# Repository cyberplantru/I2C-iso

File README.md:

##CyberPlant I2C *iso* Mini

The I2C *iso* Mini v3.0 are hot swappable digital isolators with nonlatching, bidirectional communication channels that
are compatible with I2C interfaces. This eliminates the need for
splitting I2C signals into separate transmit and receive signals
for use with standalone optocouplers. The I2C *iso* Mini provides two bidirectional channels, supporting a complete isolated I2C interface.

##Features:
- Regulated 3.3 V or 5 V output
- Up to 500 mW output power
- Bidirectional I2C communication
- input-output pull up 4k7
- Can use as Shield for Arduino Pro Mini
- PCB Size : 33.02 mm×17.78 mm

## Applications
- Isolated sensor interfaces
- Isolated I2C, SMBus, or PMBus interfaces
- Multilevel I2C interfaces
- Power supplies
- Networking
- RS-232/RS-422/RS-485 transceivers

#### Regulated 3.3 V or 5 V output

By default supply voltage set to output 5V. For use other mode need to cut copper wire on layer top and use jumper as switch

## Isolation of sensors

Use to eliminate electrical noise. The I2Ciso recommended to when reading pH and Conductivity together. Compatible with [pH Mini](https://github.com/cyberplantru/pH-Mini-v30-sample-code) and [EC Mini](EC-Mini-v30-Sample-Code). 

----------

### Package include:

-     1 x I2C iso Mini v3.0
-     2 x 12 PLS connectors
-     2 x 4 angle PLS
-     1 x jumper

----------

### Documentation:

- [Hardware](https://github.com/cyberplantru/I2C-iso/)
- [link to CyberPlant](http://www.cyber-plant.com).

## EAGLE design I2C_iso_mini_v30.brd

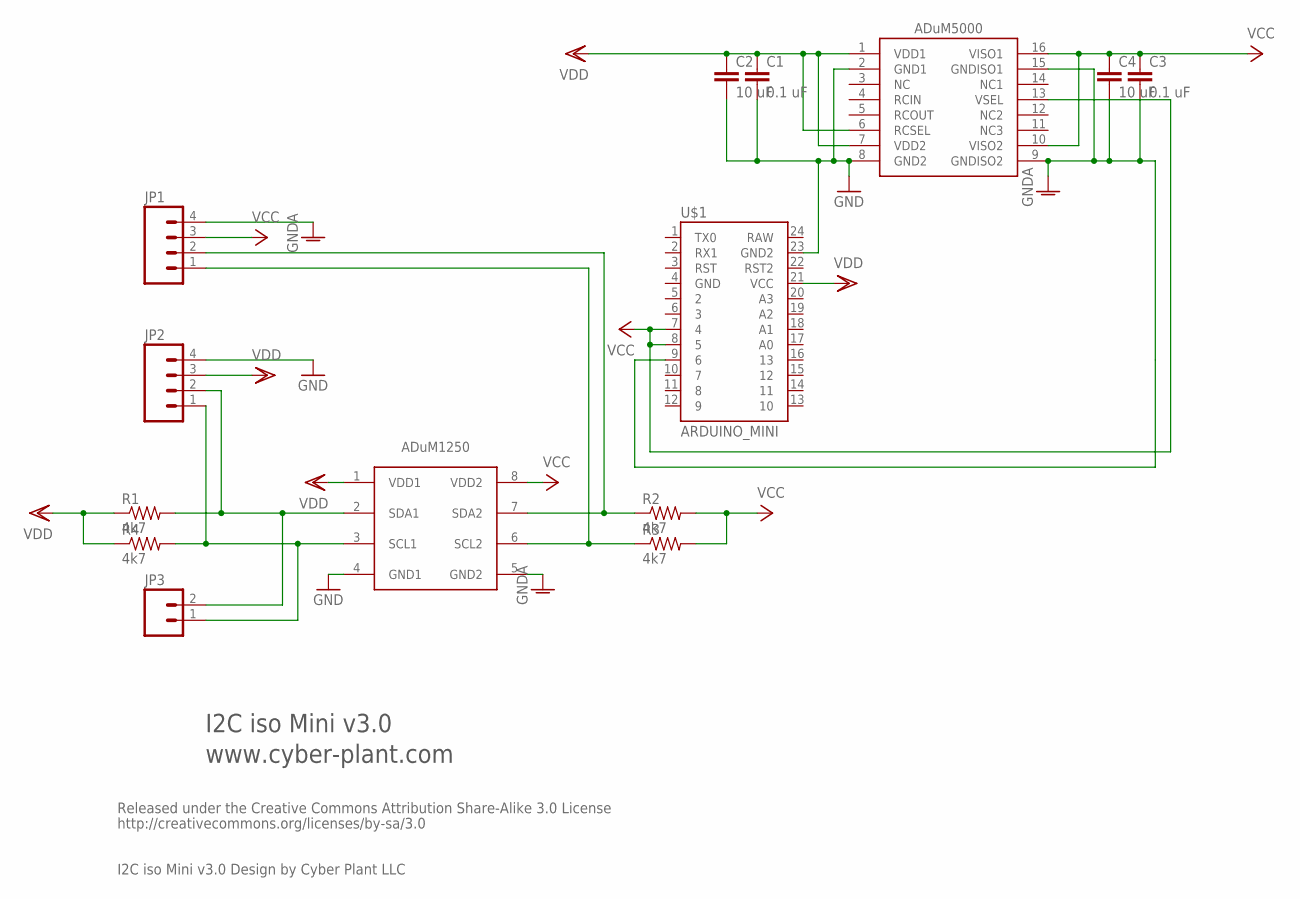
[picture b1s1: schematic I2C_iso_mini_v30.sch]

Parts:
C1, C3: 0.1 uF; 1206
C2, C4: 10 uF; 1206
JP1, JP2: M04PTH; 1X04
JP3: M02PTH; 1X02
R1, R2, R3, R4: 4k7; 1206
U$1: ARDUINO_MINI
U$3: ADUM1251; SO8
U$4: ADUM5000; SO-16W

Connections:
GND: C1.2, C2.2, JP2.4, U$1.23 (GND2), U$3.4 (GND1), U$4.2 (GND1), U$4.8 (GND2)
GNDA: C3.2, C4.2, JP1.4, U$1.9 (6), U$3.5 (GND2), U$4.9 (GNDISO2), U$4.15 (GNDISO1)
SCL: JP2.1, JP3.1, R4.2, U$3.3 (SCL1)
SCL2: JP1.1, R3.1, U$3.6 (SCL2)
SDA: JP2.2, JP3.2, R1.2, U$3.2 (SDA1)
SDA2: JP1.2, R2.1, U$3.7 (SDA2)
VCC: C3.1, C4.1, JP1.3, R2.2, R3.2, U$1.7 (4), U$1.8 (5), U$3.8 (VDD2), U$4.10 (VISO2), U$4.13 (VSEL), U$4.16 (VISO1)
VDD: C1.1, C2.1, JP2.3, R1.1, R4.1, U$1.21 (VCC), U$3.1 (VDD1), U$4.1 (VDD1), U$4.6 (RCSEL), U$4.7 (VDD2)

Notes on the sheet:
Released under the Creative Commons Attribution Share-Alike 3.0 License
http://creativecommons.org/licenses/by-sa/3.0
I2C iso Mini v3.0 Design by Cyber Plant LLC
I2C iso Mini v3.0
www.cyber-plant.com

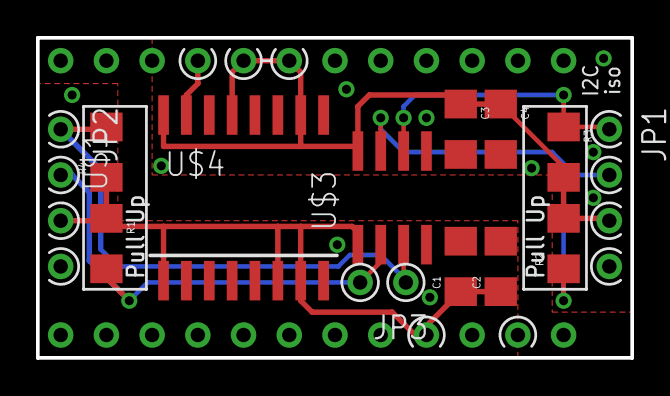
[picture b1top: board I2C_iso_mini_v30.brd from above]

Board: 2 copper layers, 33.0 x 17.8 mm, 14 parts (0 on the bottom side), 8 nets.

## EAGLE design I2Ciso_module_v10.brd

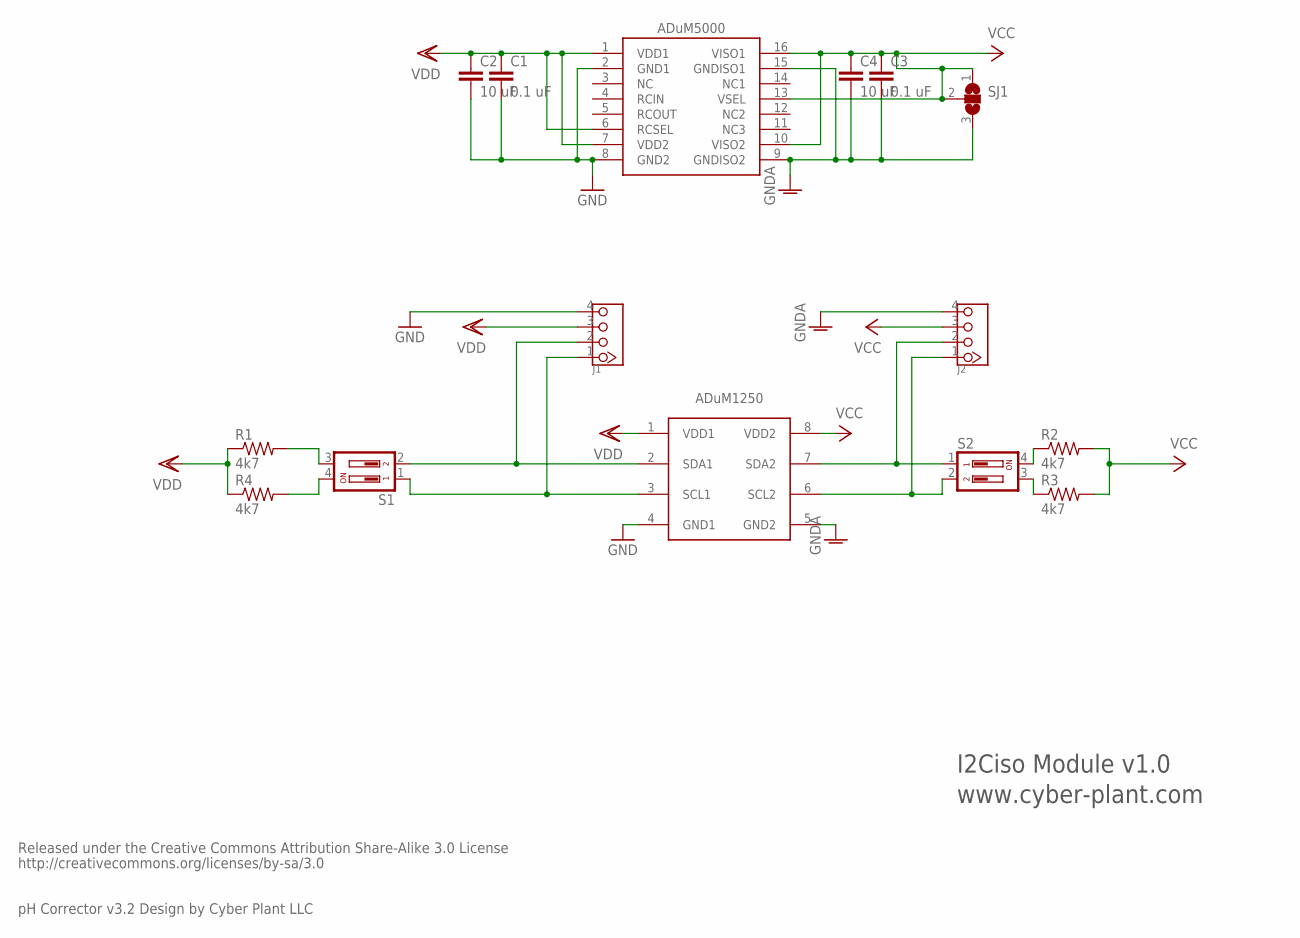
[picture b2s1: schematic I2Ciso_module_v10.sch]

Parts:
C1, C3: 0.1 uF; 1206
C2, C4: 10 uF; 1206
J1, J2: TWIG-4P-2.090D; 4P-2.0-90D
R1, R2, R3, R4: 4k7; 1206
S1, S2: DS02; DS-02
SJ1: SJ2W; SJ_2
U$3: ADUM1251; SO8
U$4: ADUM5000; SO-16W

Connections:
GND: C1.2, C2.2, J1.4, U$3.4 (GND1), U$4.2 (GND1), U$4.8 (GND2)
GNDA: C3.2, C4.2, J2.4, SJ1.3, U$3.5 (GND2), U$4.9 (GNDISO2), U$4.15 (GNDISO1)
unnamed: J1.2, S1.2, U$3.2 (SDA1)
unnamed: R3.1, S2.3
unnamed: J1.1, S1.1, U$3.3 (SCL1)
unnamed: R2.1, S2.4
unnamed: J2.2, S2.1, U$3.7 (SDA2)
unnamed: J2.1, S2.2, U$3.6 (SCL2)
unnamed: R1.2, S1.3
unnamed: R4.2, S1.4
VDD1: C1.1, C2.1, J1.3, R1.1, R4.1, U$3.1 (VDD1), U$4.1 (VDD1), U$4.6 (RCSEL), U$4.7 (VDD2)
VDD2: C3.1, C4.1, J2.3, R2.2, R3.2, SJ1.1, SJ1.2, U$3.8 (VDD2), U$4.10 (VISO2), U$4.13 (VSEL), U$4.16 (VISO1)

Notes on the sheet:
Released under the Creative Commons Attribution Share-Alike 3.0 License
http://creativecommons.org/licenses/by-sa/3.0
pH Corrector v3.2 Design by Cyber Plant LLC
I2Ciso Module v1.0
www.cyber-plant.com

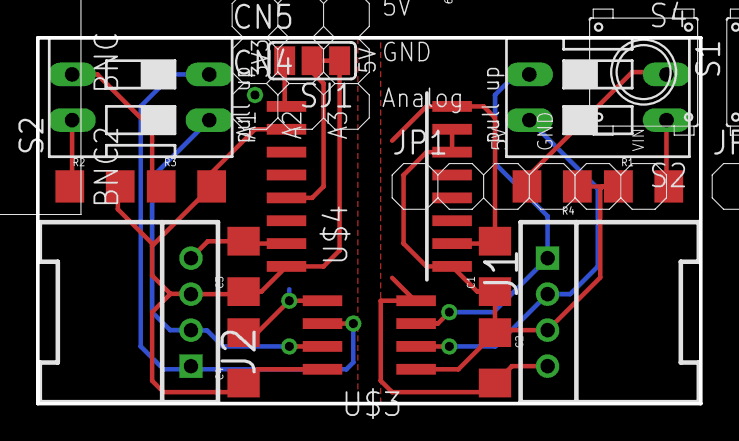
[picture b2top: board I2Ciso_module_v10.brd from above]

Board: 2 copper layers, 36.8 x 20.3 mm, 15 parts (0 on the bottom side), 12 nets.

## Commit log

2015-12-02 :boom::camel: Added .gitattributes & .gitignore files
2015-12-02 Revert ":boom::camel: Added .gitattributes & .gitignore files"
    This reverts commit 6674b92a1fe1bf1a39c21363b14bbadf96804652.
2015-12-02 Master
    isolator I2C bus
2015-12-02 master

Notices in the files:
parts and their libraries:
Arduinominimi: Licensing: CC v3.0 Share-Alike You are welcome to use this library for commercial purposes.
